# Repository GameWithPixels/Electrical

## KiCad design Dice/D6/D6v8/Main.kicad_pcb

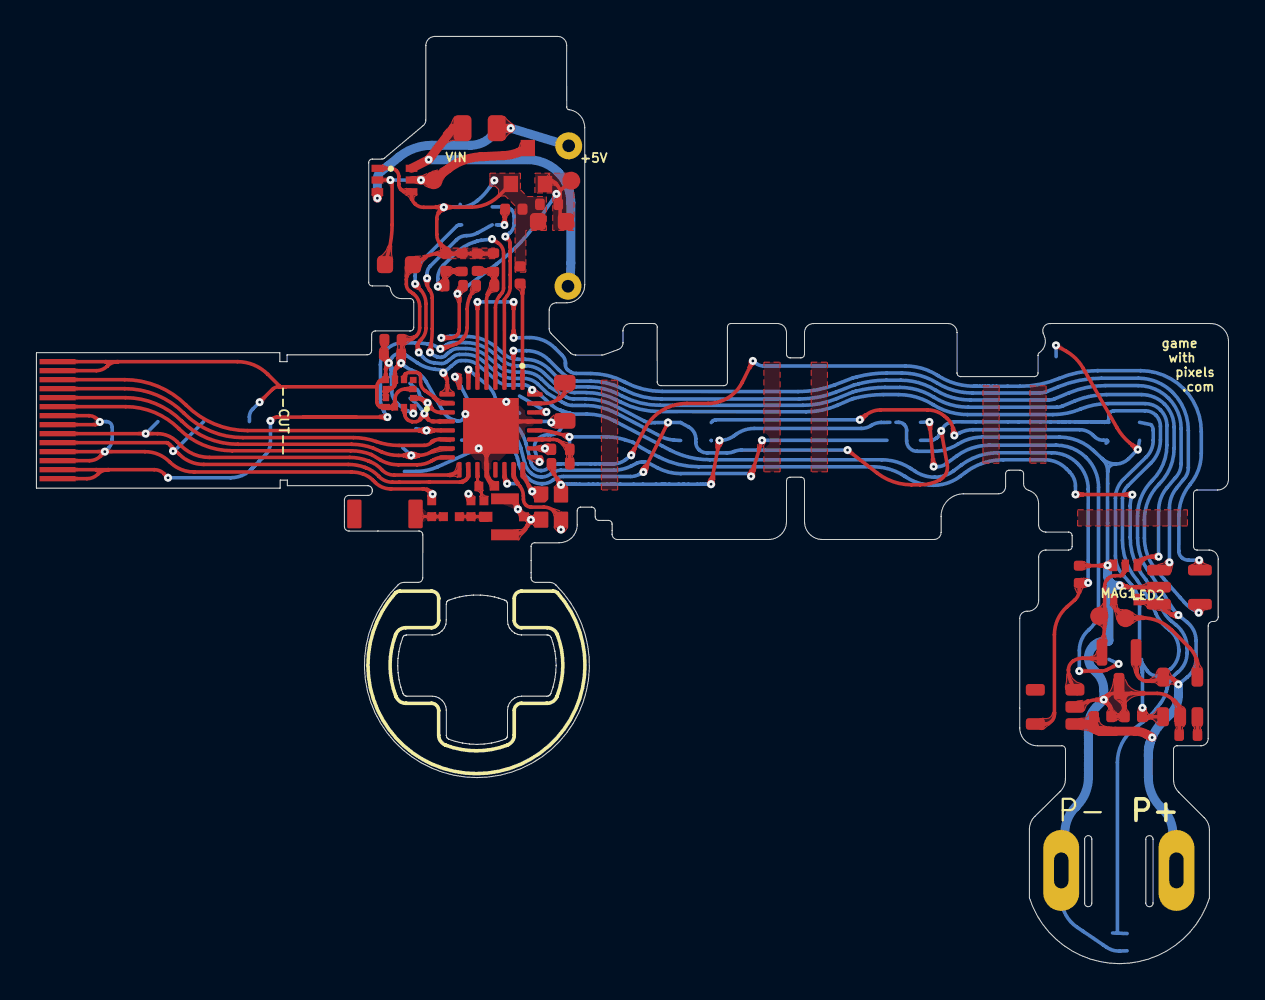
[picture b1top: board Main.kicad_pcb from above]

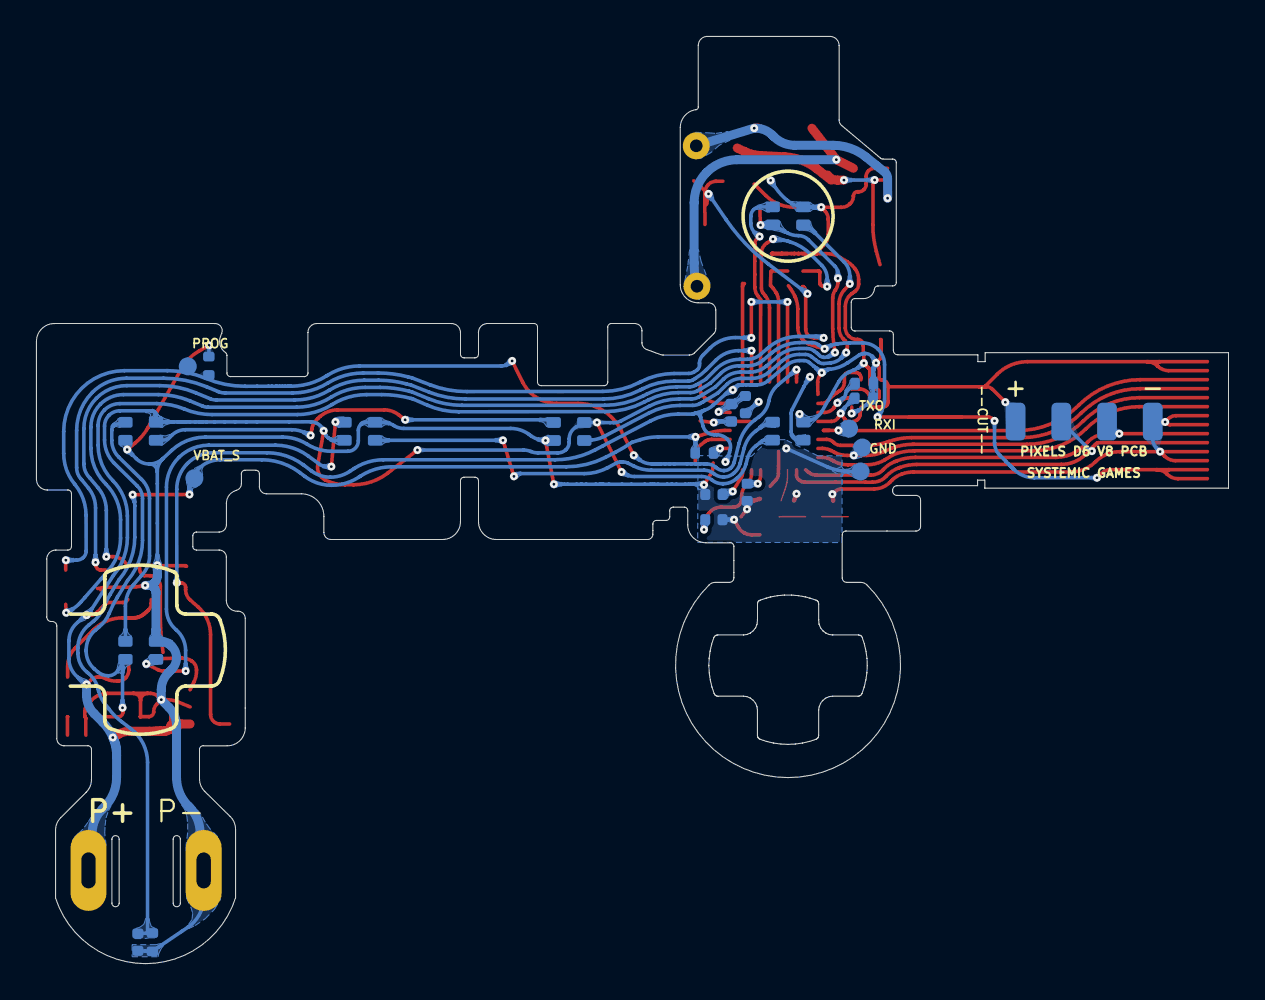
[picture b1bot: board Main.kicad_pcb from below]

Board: 2 copper layers, 66.2 x 51.5 mm, 69 parts (26 on the bottom side), 45 nets.

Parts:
AE2: Antenna_Chip; CHIP_ANT
C1, C4, C18: 4.7uF 10V 20%; C_0402_1005Metric
C2, C5: 8pF 10V 10%; C_0402_1005Metric
C3, C10, C23: 0.1uF 10V 20%; C_0402_1005Metric
C6: DNP; C_0402_1005Metric
C7: 100pF NP0 10V 5%; C_0402_1005Metric
C8: 0.8pF 10V 5% C0G; 0402_RF
C9, C16: 10uF 10V 20%; C_0402_1005Metric
C11, C12: DNP; 0402_RF
C13: 4.7uF 25V 20%; C_0603_1608Metric
C15: 22uF 10V 20%; C_0603_1608Metric
C19: 12nF 50V 5% NP0; C_0805_2012Metric
C21, C22: 10nF 25V 10%; C_0402_1005Metric
D1: BAV99S; SOT-363_SC-70-6
D2, D3, D4, D5, D6, D7: TX1812Z_2020
J1: Conn_01x14; FPC_14
J2: Conn_01x04; FPC-POGO-4
J3: Conn_01x02; Hongjie 10100 Connector
J4: DNP; MFH3.RECE.20369.001E.01
L1: 10uH 100mA 10%; L_0805_2012Metric
L2: 15nH 100mA 5%; L_0402_1005Metric
L3: 0 Ohm; 0402_RF
L5: 3.9nH 5%; 0402_RF
P5: COILA; TestPoint_THTPad_D1.5mm_Drill0.7mm_nosilk
P6: COILB; TestPoint_THTPad_D1.5mm_Drill0.7mm_nosilk
R1, R2, R7: 4.02M 1%; R_0402_1005Metric
R3: 10k 5%; R_0402_1005Metric
R4, R5, R10: 100k 1%; R_0402_1005Metric
R6: 22k 1%; R_0402_1005Metric
R8: 10M 1%; R_0402_1005Metric
R9: 120k 1%; R_0402_1005Metric
R12, R16: 2.7k 5%; R_0402_1005Metric
TH1: NTC 100k @ 25C; R_0402_1005Metric
U1: N52810_QFN32; QFN-32-1EP_5x5mm_P0.5mm_EP3.1x3.1mm
U2: KXTJ3-1057; LGA-12_2x2mm_P0.5mm
U3: PJ75AL50SA; SOT-23
U4: ME6215; SOT-23-5
U5: MCP73832T-2ACI/OT; SOT-23-5
U6: MT9700; SOT-23-5
U7: SN74LVC1G08; SOT-353_SC-70-5
U8: TMR1366; SOT-23
W1: RXI; TEST_PIN
W2: TXO; TEST_PIN
W3: PROG; TEST_PIN
W4: VBAT_S; TEST_PIN
W15: +5V; TEST_PIN
W16: VIN; TEST_PIN
W19: GND; TEST_PIN
W21: LED2; TEST_PIN
W23: MAG1_; TEST_PIN
Y1: 32MHz 40ppm; Crystal_SMD_2016-4Pin_2.0x1.6mm

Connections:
+5V: C15.1, R1.1, R4.1, U3.2 (VOUT), U5.4 (VDD), W15.1
+BATT: C16.1, J1.1, J1.2, J3.1, R7.1, U4.1 (VIN), U5.3 (VBAT), U6.5 (VIN), U7.5 (VCC), U8.1 (VCC)
/5V_SENSE: C21.1, R1.2, R2.2, U1.4 (P0.04/AIN2)
/ACC_INT: U1.10 (P0.12), U2.5 (INT)
/ANTENNA: AE2.1 (FEED), C11.1, L3.2
/ANT_50: C12.1, J4.4 (RF), L3.1, L5.2
/ANT_NRF: C8.1, L5.1, U1.19 (ANT)
/BATT_NTC: C6.1, R5.2, TH1.1, U1.28 (P0.30/AIN6), W4.1
/LED_DATA: D2.1 (DIN), U1.3 (P0.01/XL2)
/LED_EN: U1.2 (P0.00/XL1), U7.1
/LEDs/LED_RETURN_4: D5.3 (DOUT), D6.1 (DIN)
/LEDs/LED_RETURN_6: D7.3 (DOUT), U1.8 (P0.10)
/NTC_ID_VDD: R5.1, R10.2, U1.26 (P0.25)
/PROG: R6.1, U1.7 (P0.09), U5.5 (PROG), W3.1
/Power Supply/LED_EN_OUT: U6.4 (EN), U7.4, W21.1
/Power Supply/MAG1_: U4.3 (CE), U7.2, U8.2 (OUT), W23.1
/SCL: R12.2, U1.12 (P0.15), U2.12 (SCL)
/SDA: R16.2, U1.11 (P0.14), U2.2 (SDA)
/STATS: U1.6 (P0.06), U5.1 (STAT)
/VBAT_SENSE: C22.1, R7.2, R8.1, U1.5 (P0.05/AIN3)
GND: C1.2, C2.1, C3.2, C4.2, C5.1, C6.2, C7.2, C8.2, C9.2, C10.2, C11.2, C12.2, C13.2, C15.2, C16.2, C18.2, C21.2, C22.2, C23.2, D1.1 (A1), D1.4 (A3), D2.4 (GND), D3.4 (GND), D4.4 (GND), D5.4 (GND), D6.4 (GND), D7.4 (GND), J1.3, J1.4, J1.7, J1.8, J2.4, J3.2, J4.1, J4.2, J4.3, R2.1, R3.2, R4.2, R6.2, R8.2, R9.1, TH1.2, U1.20 (VSS), U1.29 (VSS), U1.33 (VSS), U2.6 (GND), U2.8 (GND), U2.9 (GND), U3.1 (VSS), U4.2 (VSS), U5.2 (VSS), U6.2 (GND), U7.3 (GND), U8.3 (GND), W19.1, Y1.2, Y1.4
unnamed: C19.2, D1.6 (K3A4), P6.1
unnamed: C19.1, D1.3 (K1A2), P5.1
unnamed: D2.3 (DOUT), D3.1 (DIN)
unnamed: D3.3 (DOUT), D4.1 (DIN)
unnamed: D4.3 (DOUT), D5.1 (DIN)
unnamed: D6.3 (DOUT), D7.1 (DIN)
unnamed: L1.2, L2.1
unnamed: L1.1, U1.31 (DCC)
unnamed: C3.1, U1.1 (DEC1)
unnamed: C7.1, U1.22 (DEC3)
unnamed: C1.1, L2.2, U1.30 (DEC4)
unnamed: R9.2, R10.1, U1.27 (P0.28/AIN4)
unnamed: C5.2, U1.23 (XC1), Y1.3
unnamed: C2.2, U1.24 (XC2), Y1.1
unnamed: R3.1, U6.3 (SET)
RESET: J1.9, U1.16 (P0.16)
RXI: J1.10, U1.15 (P0.20/TCLK), W1.1
SWDCLK: J1.6, J2.3, U1.17 (SWDCLK)
SWDIO: J1.5, J2.2, U1.18 (SWDIO)
SWO: J1.11, U1.14 (P0.18/TDATA0)
TXO: J1.12, U1.13 (P0.16/TDATA1), W2.1
VDC: C9.1, C23.1, D2.2 (VCC), D3.2 (VCC), D4.2 (VCC), D5.2 (VCC), D6.2 (VCC), D7.2 (VCC), U6.1 (VOUT)
VDD: C4.1, C10.1, C18.1, J1.13, J1.14, J2.1, R12.1, R16.1, U1.9 (VDD), U1.25 (VDD), U1.32 (VDD), U2.1 (ADDR), U2.3 (IO_VDD), U2.7 (VDD), U2.10 (VDD), U2.11 (IO_VDD), U4.5 (VOUT)
VEE: C13.1, D1.2 (K2), D1.5 (K4), U3.3 (VIN), W16.1

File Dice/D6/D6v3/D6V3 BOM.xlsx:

Item | Qty | Reference(s) | Value | Footprint | Generic OK | Manufacturer | Manufacturer Part Number
1 | 1 | AE2 | Antenna_Chip | Pixels-dice:CHIP_ANT | NO | Microgate | MGMA3216H2450-A02
2 | 4 | C1, C4, C15, C18 | 4.7uF 6.3V 20% | Capacitor_SMD:C_0402_1005Metric | YES | Murata | GRM155R60J475ME87D
3 | 2 | C2, C5 | 8pF 10V 10% | Capacitor_SMD:C_0402_1005Metric | YES | Murata | GRT1555C2A8R0DA02
4 | 3 | C3, C10, C23 | 0.1uF 10V 20% | Capacitor_SMD:C_0402_1005Metric | YES | Murata | GRM155R61H104KE19D
5 | 3 | C6, C21, C22 | 10nF 25V 10% | Capacitor_SMD:C_0402_1005Metric | YES | Murata | GRM155R71H103KA88
6 | 1 | C7 | 100pF NP0 10V 5% | Capacitor_SMD:C_0402_1005Metric | YES | Murata | GCM1555C1H101JA16J
7 | 1 | C8 | 0.8pF 10V 5% C0G | Pixels-dice:0402_RF | YES | Murata | GJM1555C1HR80BB01
8 | 2 | C9, C16 | 10uF 6.3V 20% | Pixels-dice:C_0402_1005Metric | YES | Murata | GRM155R60J106ME05J
10 | 1 | C12 | 0.5pF 10V 5% C0G | Pixels-dice:0402_RF | YES | Murata | GJM1555C1HR50BB01
11 | 1 | C13 | 4.7uF 25V 20% | Capacitor_SMD:C_0603_1608Metric | YES | Murata | GRM188R61E475KE11D
12 | 1 | C17 | 22pF 10V 5% | Capacitor_SMD:C_0402_1005Metric | YES | Murata | GCM1555C1H220JA16J
13 | 1 | C19 | 33nF 50V 5% NP0 | Capacitor_SMD:C_1206_3216Metric | YES | Murata | GRM3195C1H333JA01J
14 | 1 | D1 | BAV99S | Package_TO_SOT_SMD:SOT-363_SC-70-6 | YES | Nexperia | BAV99S,115
15 | 6 | D2, D3, D4, D5, D6, D7 | TX1812Z_2020 | Pixels-dice:TX1812Z_2020 | NO | TCWIN | TX1812Z 2020
20 | 1 | L1 | 10uH 100mA 10% | Inductor_SMD:L_0805_2012Metric | YES | Murata | LQM21FN100M80L
21 | 1 | L2 | 15nH 100mA 5% | Inductor_SMD:L_0402_1005Metric | YES | Murata | LQG15HS15NJ02D
22 | 1 | L3 | 1.8nH 5% | Pixels-dice:0402_RF | YES | Murata | LQG15HZ1N8C02D
23 | 1 | L4 | 2.2uH 20mA 10% | Inductor_SMD:L_0805_2012Metric | YES | Murata | LQM21PN2R2MC0
24 | 1 | L5 | 3.9nH 5% | Pixels-dice:0402_RF | YES | Murata | LQG15HS3N9B02D
27 | 3 | R1, R7, R13 | 4.02M 1% | Resistor_SMD:R_0402_1005Metric | YES | UNI-ROYAL(Uniroyal Elec) | 0402WGF4024TCE
28 | 3 | R2, R8, R14 | 10M 1% | Resistor_SMD:R_0402_1005Metric | YES | UNI-ROYAL(Uniroyal Elec) | 0402WGF1005TCE
29 | 1 | R3 | 10k 5% | Resistor_SMD:R_0402_1005Metric | YES | UNI-ROYAL(Uniroyal Elec) | 0402WGJ0103TCE
30 | 1 | R4 | 402k 1% | Resistor_SMD:R_0402_1005Metric | YES | UNI-ROYAL(Uniroyal Elec) | 0402WGF4023TCE
31 | 2 | R5, R10 | 100k 1% | Resistor_SMD:R_0402_1005Metric | YES | UNI-ROYAL(Uniroyal Elec) | 0402WGF1003TCE
32 | 1 | R6 | 22k 1% | Resistor_SMD:R_0402_1005Metric | YES | UNI-ROYAL(Uniroyal Elec) | 0402WGF2202TCE
33 | 1 | R9 | 120k 1% | Resistor_SMD:R_0402_1005Metric | YES | UNI-ROYAL(Uniroyal Elec) | 0402WGF1203TCE
34 | 2 | R12, R16 | 2.7k 5% | Resistor_SMD:R_0402_1005Metric | YES | UNI-ROYAL(Uniroyal Elec) | 0402WGJ0272TCE
35 | 1 | U1 | N52810_QFN32 | Package_DFN_QFN:QFN-32-1EP_5x5mm_P0.5mm_EP3.1x3.1mm | NO | Nordic Semiconductor | NRF52810-QCAA-R
36 | 1 | U2 | KXTJ3-1057 | Package_LGA:LGA-12_2x2mm_P0.5mm | NO | Kionix | KXTJ3-1057
37 | 1 | U3 | PJ75AL50SA | Pixels-dice:SOT-23 | NO | PJSEMI | PJ75AL50SA
38 | 1 | U4 | LN3435 | Pixels-dice:SOT-23-5 | NO | NATLINEAR | LN3435
39 | 1 | U5 | MCP73832T-2ACI/OT | Package_TO_SOT_SMD:SOT-23-5 | NO | Microchip | MCP73832T-2ACI/OT
40 | 1 | U6 | MT9700 | Pixels-dice:SOT-23-5 | NO | XI'AN Aerosemi Tech | MT9700
41 | 1 | U7 | 74AHC1G08 | Pixels-dice:SOT-353_SC-70-5 | YES | Texas Instruments | SN74AHC1G08DCKR
42 | 1 | U8 | TMR1366 | Package_TO_SOT_SMD:SOT-23 | NO | Multi Dimension | TMR1366S
62 | 1 | Y1 | 32MHz 40ppm | Pixels-dice:Crystal_SMD_2016-4Pin_2.0x1.6mm | YES | Murata | XRCGB32M000F2P00R0
